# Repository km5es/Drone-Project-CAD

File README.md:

# Drone-Project-3D
This repository contains 3D CAD models, pcb designs, and RF simulation files for a drone-based antenna calibrator entitled Precision Radio Instrument for Antenna Measurements (PRIAM). Its chief application is towards 21-cm cosmology and low-frequency radio instruments. The entire drone-based experiment is represented in the following block diagram:

>[!TIP]
>* A complete [Gitbook](app.gitbook.com) guide can be found here:\
>     https://krishnamakhija.gitbook.io/priam/
>* The repo containing the ROS and SDR code along with the flight path generator can be found [here](https://github.com/km5es/Drone-Project-code.git).

Two drones have been developed, one with a Flamewheel F450 frame and one with a Tarot T960 frame.

## Flamewheel F450

A scaled down drone for experimentation and testing. This was used for testing the custom ROS nodes, RTK performance, and new versions of the flight stack. This was also used to evaluate potential features and upgrades such as RPM-based gyro filtering, and system model verification.

### Drone 
* Flamewheel F450 frame,
* DJI 2312E 960 KV motors,
* DJI 9450 propellers,
* APD 80A F-Series 80F3[X] ESC,
* Pixhawk 2.1 CubeOrange,
* Drotek F9P-based RTK GPS,
* Maxbotix MB1242 SONAR,
* FrSky X8R radio,
* 915 MHz SiK telemetry,
* 4S 4500 mAh Li-Po battery.

### Payload
* ODROID XU4 single-board computer

## PRIAM (Tarot T960)

The actual experiment will be carried out on a larger drone capable of bearing the entire payload. It will be capable of extremely precise magnitude and phase measurements of an antenna-under-test (AUT) using a [custom-developed autonomous calibration routine](https://github.com/km5es/Drone-Project-code). Here are some of its hardware specifications:

### Drone
* Tarot T960 frame,
* APD 80A F-Series 80F3[X] ESC,
* Tarot 5008 High Power Brushless Motor (340kv),
* Tarot 1855 props,
* 12Ah battery -- about 35-40 mins of endurance expected,
* 12 kgs of total weight capacity,
* Retractable landing gear,
* Drotek F9P-based RTK GPS,
* Pixhawk 2.4.8 flight controller,
* 915 MHz SiK telemetry,
* 2.4 GHz X8R radio,
* Maxbotix MB1242 SONAR.

### Payload
* Raspberry Pi 4B payload computer with UPS and separate battery,
* Ettus B205-mini software-defined radio (70 MHz - 6 GHz),
* Custom RF circuitry: RF switch, and dual-pol balun,
* Dual-polarization, half-wavelength, telescopic, crossed-dipoles (70 MHz - 1 GHz),
* High accuracy frequency reference (phase payload)

Complete CAD models and further details are to be found in the [CAD Files](/CAD_Files) folder. That folder also contains drawings and Inventor files for custom parts for both drones. 

In addition, several RF modules have been designed. 

## RF modules
### Switches

Two switches have been designed:
* A simple switch to enable X- and Y- polarization calibration (left) and
* A network of RF switches to enable X-, Y- and circular-polarized calibration (right).

<br><br><br><br><br><br><br><br><br><br><br><br><br><br><br>

### Balun

There is also a dual-pol vertically oriented balun included in this repository. 

<br><br><br><br><br><br><br><br><br><br><br><br><br><br><br><br>
<br><br><br><br>

Microwave Office (MWO), Eagle, and Fusion360 files of these components are included in the [RF Related](/RF_Related) folder. Details of each are in nested `README.md` files. 

>***NOTE:*** Several sub-assemblies and parts in the 3D models have been obtained from [GrabCAD](https://grabcad.com/). None of the work in this repo is towards commercialization or monetary profit. However, credit is due to the creators of those files anyway.

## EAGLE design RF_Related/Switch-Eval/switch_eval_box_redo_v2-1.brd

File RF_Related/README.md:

# RF-related files
This folder contains:
* MWO simulation files of the polarization switch - a network of RF switches, amplifiers, and filters that enables switching from linear X to linear Y polarization and then to circular polarization using the payload computer's GPIO.
* Eagle files for the polarization switch and a simple RF switch which is used for simply switching from linear X to linear Y polarization (for cross-polarization calibration only).
* Eagle, Inventor and Fusion360 files of the dual-pol balun candidates.

## Polarization switch
Below is a block diagram of the full polarization switch. Its purpose is to enable cross-polarization, co-polarization and circular polarization calibrations of the antenna under test. It will also facilitate multipath corrections and improve SNR by 10 dB bringing the total ouput power of the transmitter up to +20 dBm.

There should be three circuit boards: for a low-band (60 - 90 MHz), mid-band (120 - 150 MHz), and a high-band mode (190 - 250 MHz). [This](pol_switch.emp) file has the MWO simulations of the low-band version of the polarization switch. Here are the S-parameters (simulation only) of the low-band switch in circular polarization mode:

The BOM (not comprehensive right now, does not contain Mini Circuits components) is attached [here](ShopCart.csv). 

There is also a simpler version of the switch added [here](Switch-Eval/). This is simply an evaluation board of the [HSWA2-30DR+][switch] switch from Mini Circuits. This will only enable linear-X and linear-Y measurements. The boxes that I have chosen to house the PCBs are linked [here][hammond_box_large] and [here][hammond_box_small]. Fusion360 files soon to follow. This is what the boards look like right now (eval and full pol switch).

<br><br><br><br><br><br><br><br><br><br><br><br><br><br><br>

## Balun
This folder also contains 3D CAD models and Eagle PCB design files of the dual-pol balun. The balun is a vertically oriented dual-pol design using two separate PCBs with a 2:1 turns ratio [transformer][trans]. The box I am considering is linked [here][balun-box]. Here is what it looks like:

[hammond_box_large]: https://www.hammfg.com/part/1590Z062BK?referer=526
[hammond_box_small]: https://www.hammfg.com/part/1590Z061BK
[switch]: https://www.minicircuits.com/WebStore/dashboard.html?model=HSWA2-30DR%2B
[balun-box]: https://www.davantech.com/product/d1001433-electronic-project-box-52w38h80l/
[trans]: https://www.minicircuits.com/WebStore/dashboard.html?model=ADT2-1T%2B

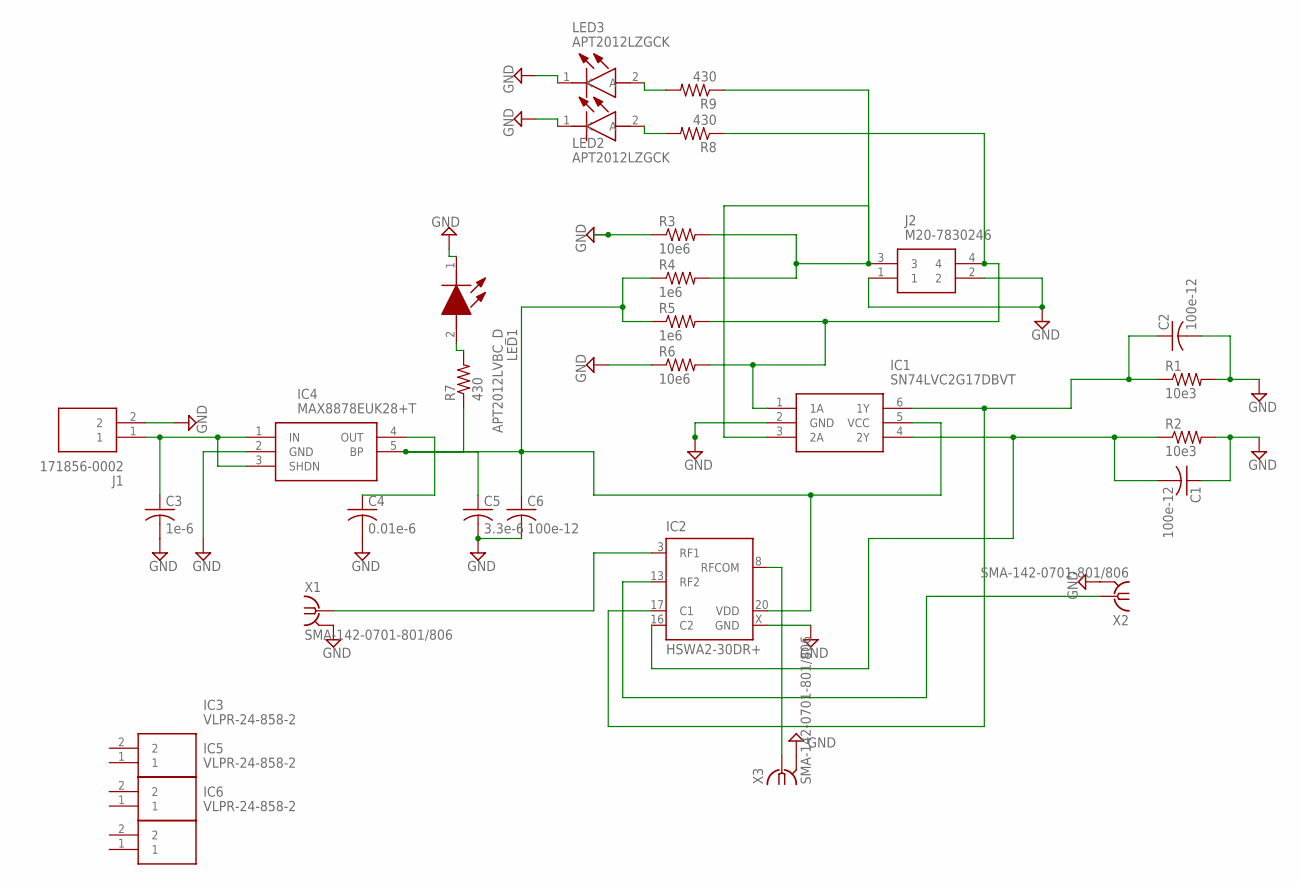
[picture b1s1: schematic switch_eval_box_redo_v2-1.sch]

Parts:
C1, C2, C6: 100e-12; C0603
C3: 1e-6; C0603
C4: 0.01e-6; C0603
C5: 3.3e-6; C0603
IC1: SN74LVC2G17DBVT; SOT95P280X145-6N
IC2: HSWA2-30DR+; DG983-1
IC3, IC5, IC6: VLPR-24-858-2; VLPR248582
IC4: MAX8878EUK28+T; SOT95P280X145-5N
J1: 171856-0002; SHDR2W90P0X254_1X2_493X635X106
J2: M20-7830246; M207830246
LED1: APT2012LVBC_D; LEDC2012X85N
LED2, LED3: APT2012LZGCK; LEDC2012X85N
R1, R2: 10e3; R0603
R3, R6: 10e6; R0603
R4, R5: 1e6; R0603
R7, R8, R9: 430; R0603
X1, X2, X3: SMA-142-0701-801/806; J502-ND-142-0701-801/806

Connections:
GND: C1.1, C2.2, C3.2, C4.2, C5.2, C6.2, IC1.2 (GND), IC2.1 (GND), IC2.2 (GND), IC2.4 (GND), IC2.5 (GND), IC2.6 (GND), IC2.7 (GND), IC2.9 (GND), IC2.10 (GND), IC2.11 (GND), IC2.12 (GND), IC2.14 (GND), IC2.15 (GND), IC2.18 (GND), IC2.19 (GND), IC2.X (GND), IC4.2 (GND), J1.2, J2.1, J2.2, LED1.1 (K), LED2.1 (K), LED3.1 (K), R1.2, R2.2, R3.1, R6.1, X1.G@1 (2), X1.G@2 (2), X1.G@3 (2), X1.G@4 (2), X2.G@1 (2), X2.G@2 (2), X2.G@3 (2), X2.G@4 (2), X3.G@1 (2), X3.G@2 (2), X3.G@3 (2), X3.G@4 (2)
unnamed: IC1.3 (2A), J2.3, R3.2, R4.2, R9.1
unnamed: C3.1, IC4.1 (IN), IC4.3 (SHDN), J1.1
unnamed: C4.1, IC4.4 (OUT)
unnamed: IC1.1 (1A), J2.4, R5.2, R6.2, R8.1
unnamed: LED1.2 (A), R7.2
unnamed: LED3.2 (A), R9.2
unnamed: C5.1, C6.1, IC1.5 (VCC), IC2.20 (VDD), IC4.5 (BP), R4.1, R5.1, R7.1
unnamed: IC2.3 (RF1), X1.1
unnamed: C2.1, IC1.6 (1Y), IC2.17 (C1), R1.1
unnamed: IC2.13 (RF2), X2.1
unnamed: C1.2, IC1.4 (2Y), IC2.16 (C2), R2.1
unnamed: IC2.8 (RFCOM), X3.1
unnamed: LED2.2 (A), R8.2

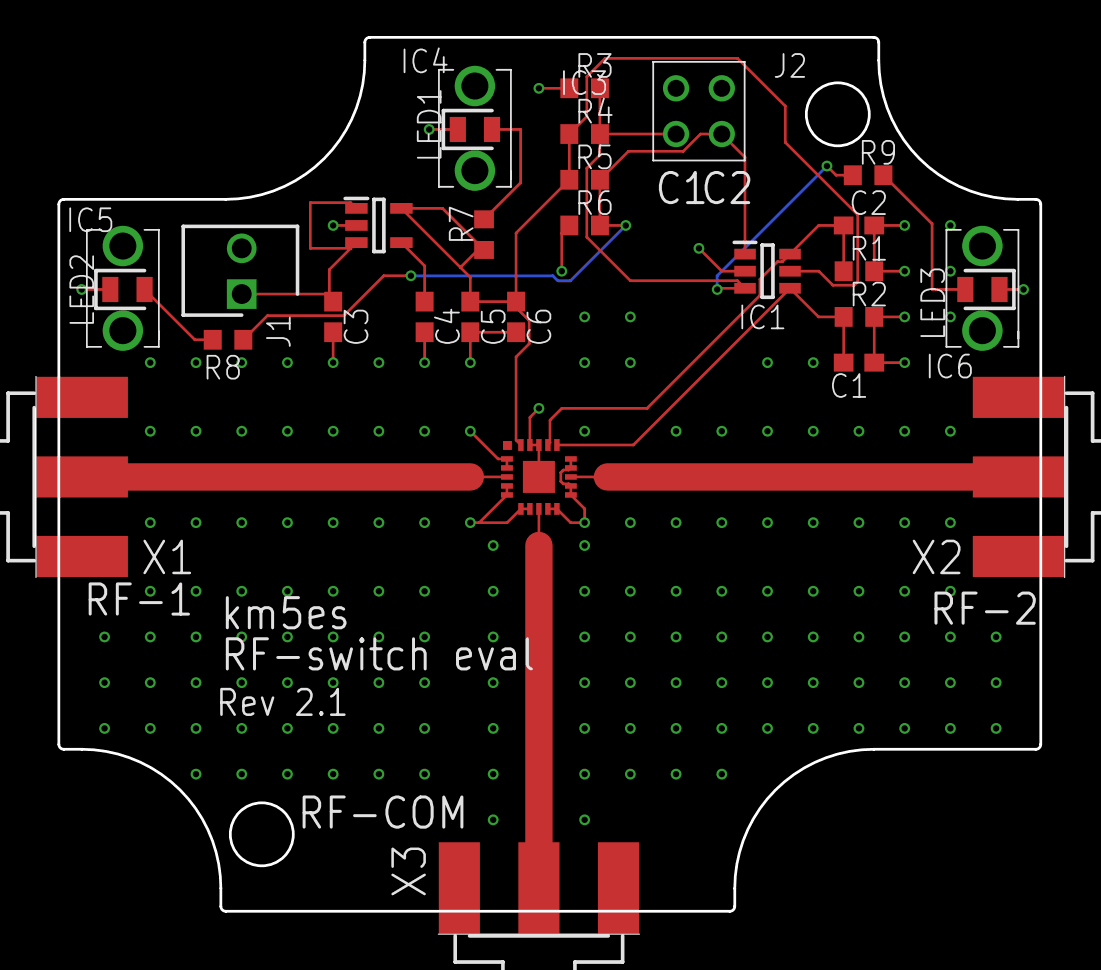
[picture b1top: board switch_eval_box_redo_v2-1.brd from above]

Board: 2 copper layers, 57.2 x 49.8 mm, 29 parts (0 on the bottom side), 14 nets.

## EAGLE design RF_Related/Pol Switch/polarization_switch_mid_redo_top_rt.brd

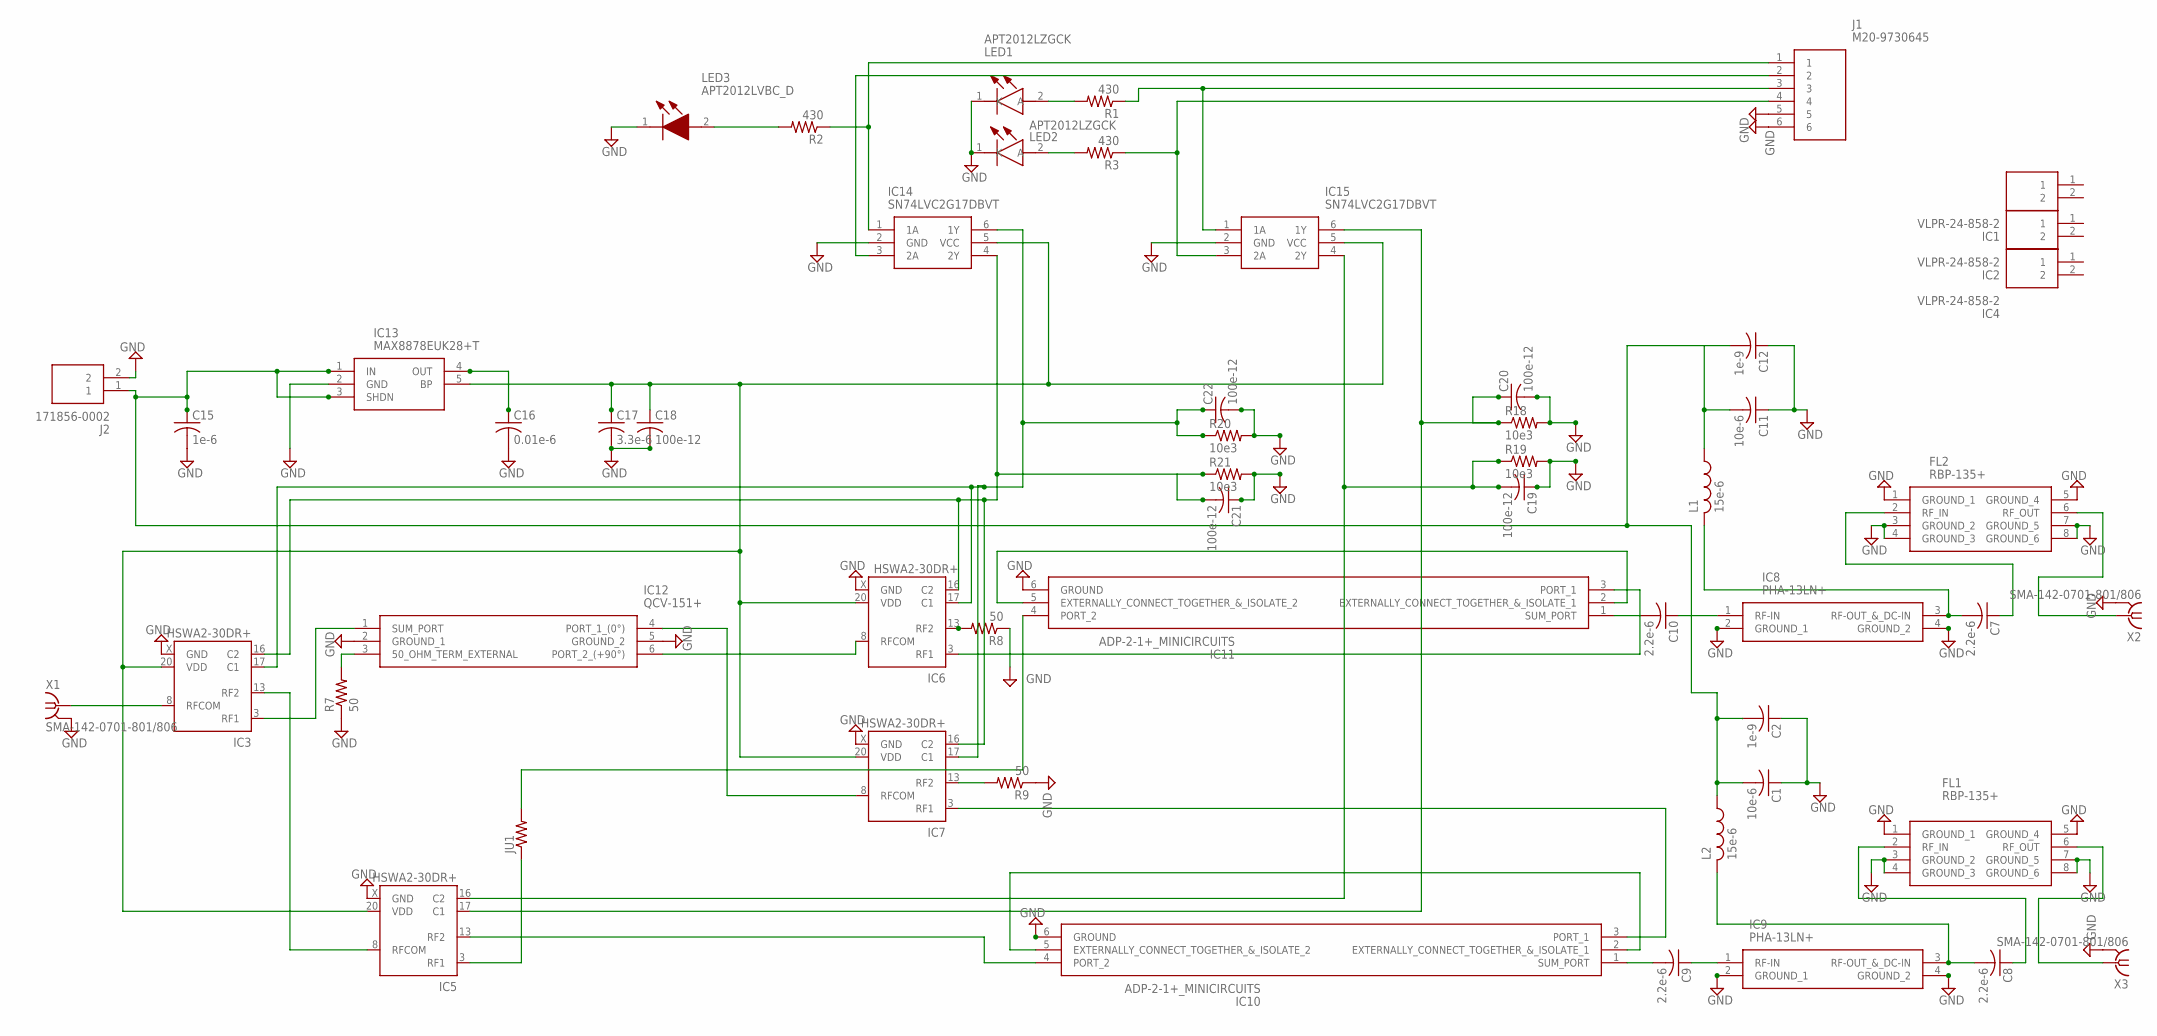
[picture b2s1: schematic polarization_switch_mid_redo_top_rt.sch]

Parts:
C1, C11: 10e-6; C0603
C2, C12: 1e-9; C0603
C7, C8, C9, C10: 2.2e-6; C0603
C15: 1e-6; C0603
C16: 0.01e-6; C0603
C17: 3.3e-6; C0603
C18, C19, C20, C21, C22: 100e-12; C0603
FL1, FL2: RBP-135+; RBP135
IC1, IC2, IC4: VLPR-24-858-2; VLPR248582
IC3, IC5, IC6, IC7: HSWA2-30DR+; DG983-1
IC8, IC9: PHA-13LN+; PHA13LN
IC10, IC11: ADP-2-1+_MINICIRCUITS; SOTFL254P691X411-6N
IC12: QCV-151+; QCV151
IC13: MAX8878EUK28+T; SOT95P280X145-5N
IC14, IC15: SN74LVC2G17DBVT; SOT95P280X145-6N
J1: M20-9730645; HDRV6W66P0X254_1X6_1524X254X96
J2: 171856-0002; SHDR2W90P0X254_1X2_493X635X106
JU1: R-US_R1206; R1206
L1, L2: 15e-6; L3225M
LED1, LED2: APT2012LZGCK; LEDC2012X85N
LED3: APT2012LVBC_D; LEDC2012X85N
R1, R2, R3: 430; R0603
R7, R8, R9: 50; R0603
R18, R19, R20, R21: 10e3; R0603
X1, X2, X3: SMA-142-0701-801/806; J502-ND-142-0701-801/806

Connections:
GND: C1.1, C2.1, C11.1, C12.1, C15.2, C16.2, C17.2, C18.2, C19.1, C20.2, C21.1, C22.2, FL1.1 (GROUND_1), FL1.3 (GROUND_2), FL1.4 (GROUND_3), FL1.5 (GROUND_4), FL1.7 (GROUND_5), FL1.8 (GROUND_6), FL2.1 (GROUND_1), FL2.3 (GROUND_2), FL2.4 (GROUND_3), FL2.5 (GROUND_4), FL2.7 (GROUND_5), FL2.8 (GROUND_6), IC3.1 (GND), IC3.2 (GND), IC3.4 (GND), IC3.5 (GND), IC3.6 (GND), IC3.7 (GND), IC3.9 (GND), IC3.10 (GND), IC3.11 (GND), IC3.12 (GND), IC3.14 (GND), IC3.15 (GND), IC3.18 (GND), IC3.19 (GND), IC3.X (GND), IC5.1 (GND), IC5.2 (GND), IC5.4 (GND), IC5.5 (GND), IC5.6 (GND), IC5.7 (GND), IC5.9 (GND), IC5.10 (GND), IC5.11 (GND), IC5.12 (GND), IC5.14 (GND), IC5.15 (GND), IC5.18 (GND), IC5.19 (GND), IC5.X (GND), IC6.1 (GND), IC6.2 (GND), IC6.4 (GND), IC6.5 (GND), IC6.6 (GND), IC6.7 (GND), IC6.9 (GND), IC6.10 (GND), IC6.11 (GND), IC6.12 (GND), IC6.14 (GND), IC6.15 (GND), IC6.18 (GND), IC6.19 (GND), IC6.X (GND), IC7.1 (GND), IC7.2 (GND), IC7.4 (GND), IC7.5 (GND), IC7.6 (GND), IC7.7 (GND), IC7.9 (GND), IC7.10 (GND), IC7.11 (GND), IC7.12 (GND), IC7.14 (GND), IC7.15 (GND), IC7.18 (GND), IC7.19 (GND), IC7.X (GND), IC8.2 (GROUND_1), IC8.4 (GROUND_2), IC9.2 (GROUND_1), IC9.4 (GROUND_2), IC10.6 (GROUND), IC11.6 (GROUND), IC12.2 (GROUND_1), IC12.5 (GROUND_2), IC13.2 (GND), IC14.2 (GND), IC15.2 (GND), J1.5, J1.6, J2.2, LED1.1 (K), LED2.1 (K), LED3.1 (K), R7.1, R8.1, R9.1, R18.2, R19.2, R20.2, R21.2, X1.G@1 (2), X1.G@2 (2), X1.G@3 (2), X1.G@4 (2), X2.G@1 (2), X2.G@2 (2), X2.G@3 (2), X2.G@4 (2), X3.G@1 (2), X3.G@2 (2), X3.G@3 (2), X3.G@4 (2)
unnamed: LED2.2 (A), R3.2
unnamed: LED1.2 (A), R1.2
unnamed: LED3.2 (A), R2.2
unnamed: IC5.13 (RF2), IC10.4 (PORT_2)
unnamed: IC3.8 (RFCOM), X1.1
unnamed: C10.2, IC11.1 (SUM_PORT)
unnamed: IC7.3 (RF1), IC10.3 (PORT_1)
unnamed: C20.1, IC5.17 (C1), IC15.6 (1Y), R18.1
unnamed: IC7.8 (RFCOM), IC12.4 (PORT_1_(0°))
unnamed: IC11.4 (PORT_2), JU1.2
unnamed: IC6.3 (RF1), IC11.3 (PORT_1)
unnamed: IC5.3 (RF1), JU1.1
unnamed: C10.1, IC8.1 (RF-IN)
unnamed: IC3.3 (RF1), IC12.1 (SUM_PORT)
unnamed: IC3.13 (RF2), IC5.8 (RFCOM)
unnamed: IC6.8 (RFCOM), IC12.6 (PORT_2_(+90°))
unnamed: IC6.13 (RF2), R8.2
unnamed: C7.2, IC8.3 (RF-OUT_&_DC-IN), L1.2
unnamed: C9.2, IC10.1 (SUM_PORT)
unnamed: IC11.2 (EXTERNALLY_CONNECT_TOGETHER_&_ISOLATE_1), IC11.5 (EXTERNALLY_CONNECT_TOGETHER_&_ISOLATE_2)
unnamed: IC10.2 (EXTERNALLY_CONNECT_TOGETHER_&_ISOLATE_1), IC10.5 (EXTERNALLY_CONNECT_TOGETHER_&_ISOLATE_2)
unnamed: C9.1, IC9.1 (RF-IN)
unnamed: C8.2, IC9.3 (RF-OUT_&_DC-IN), L2.2
unnamed: C7.1, FL2.2 (RF_IN)
unnamed: FL2.6 (RF_OUT), X2.1
unnamed: C8.1, FL1.2 (RF_IN)
unnamed: FL1.6 (RF_OUT), X3.1
unnamed: IC12.3 (50_OHM_TERM_EXTERNAL), R7.2
unnamed: IC7.13 (RF2), R9.2
unnamed: C1.2, C2.2, C11.2, C12.2, C15.1, IC13.1 (IN), IC13.3 (SHDN), J2.1, L1.1, L2.1
unnamed: IC14.1 (1A), J1.1, R2.1
unnamed: C19.2, IC5.16 (C2), IC15.4 (2Y), R19.1
unnamed: C17.1, C18.1, IC3.20 (VDD), IC5.20 (VDD), IC6.20 (VDD), IC7.20 (VDD), IC13.5 (BP), IC14.5 (VCC), IC15.5 (VCC)
unnamed: C16.1, IC13.4 (OUT)
unnamed: C22.1, IC3.17 (C1), IC6.17 (C1), IC7.17 (C1), IC14.6 (1Y), R20.1
unnamed: IC14.3 (2A), J1.2
unnamed: IC15.1 (1A), J1.3, R1.1
unnamed: IC15.3 (2A), J1.4, R3.1
unnamed: C21.2, IC3.16 (C2), IC6.16 (C2), IC7.16 (C2), IC14.4 (2Y), R21.1

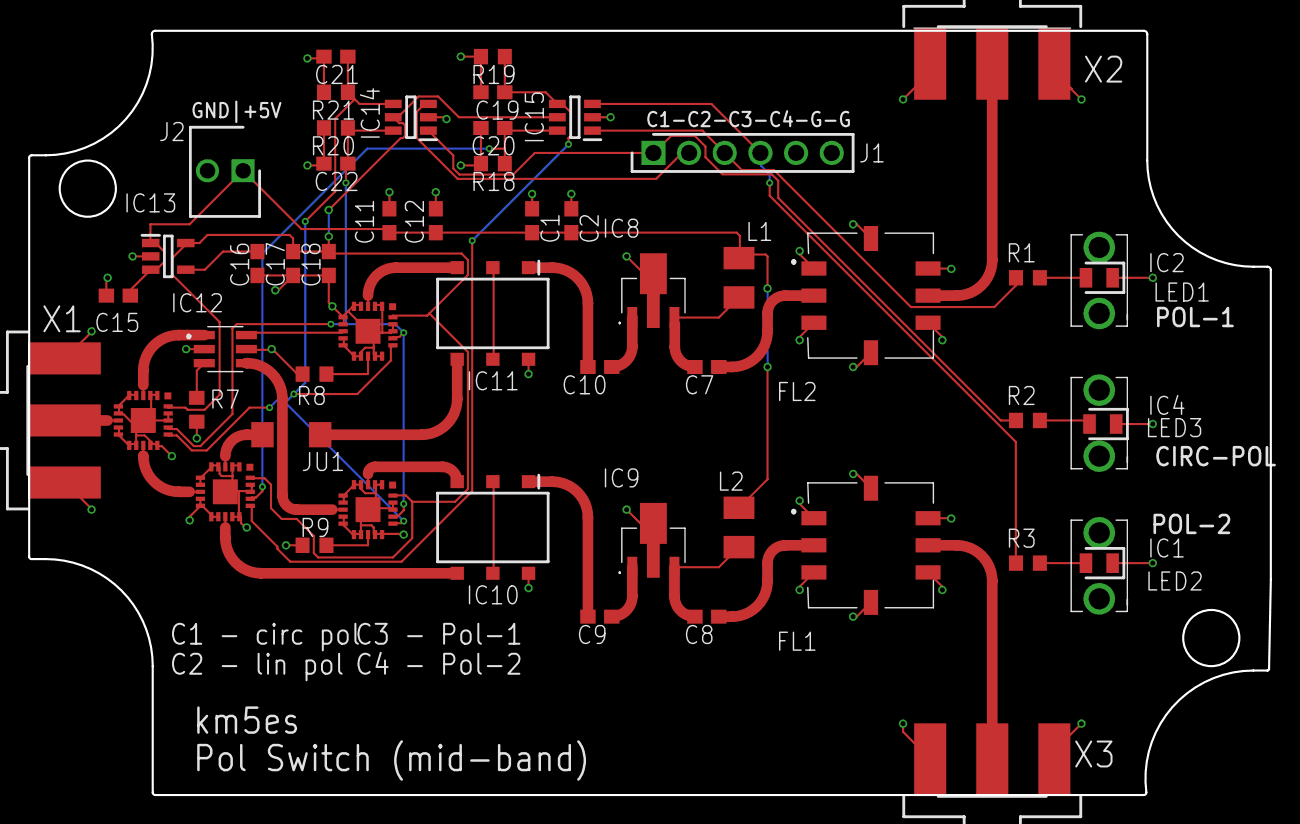
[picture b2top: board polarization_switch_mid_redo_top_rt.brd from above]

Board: 2 copper layers, 88.4 x 54.4 mm, 54 parts (0 on the bottom side), 40 nets.

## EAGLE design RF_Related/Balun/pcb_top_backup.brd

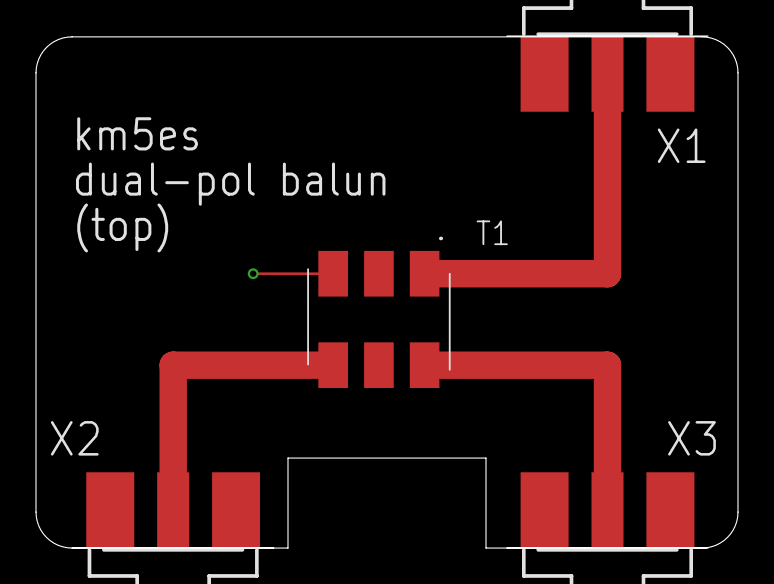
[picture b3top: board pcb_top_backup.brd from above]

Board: 2 copper layers, 39.0 x 28.4 mm, 4 parts (0 on the bottom side), 4 nets.

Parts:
T1: ADT1-1WT+; ADT11WT
X1, X2, X3: SMA-142-0711-821/826; J502-ND-142-0711-821/826

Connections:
GND: T1.3, X1.G@1, X1.G@2, X1.G@3, X1.G@4, X2.G@1, X2.G@2, X2.G@3, X2.G@4, X3.G@1, X3.G@2, X3.G@3, X3.G@4
unnamed: T1.1, X1.1
unnamed: T1.6, X3.1
unnamed: T1.4, X2.1

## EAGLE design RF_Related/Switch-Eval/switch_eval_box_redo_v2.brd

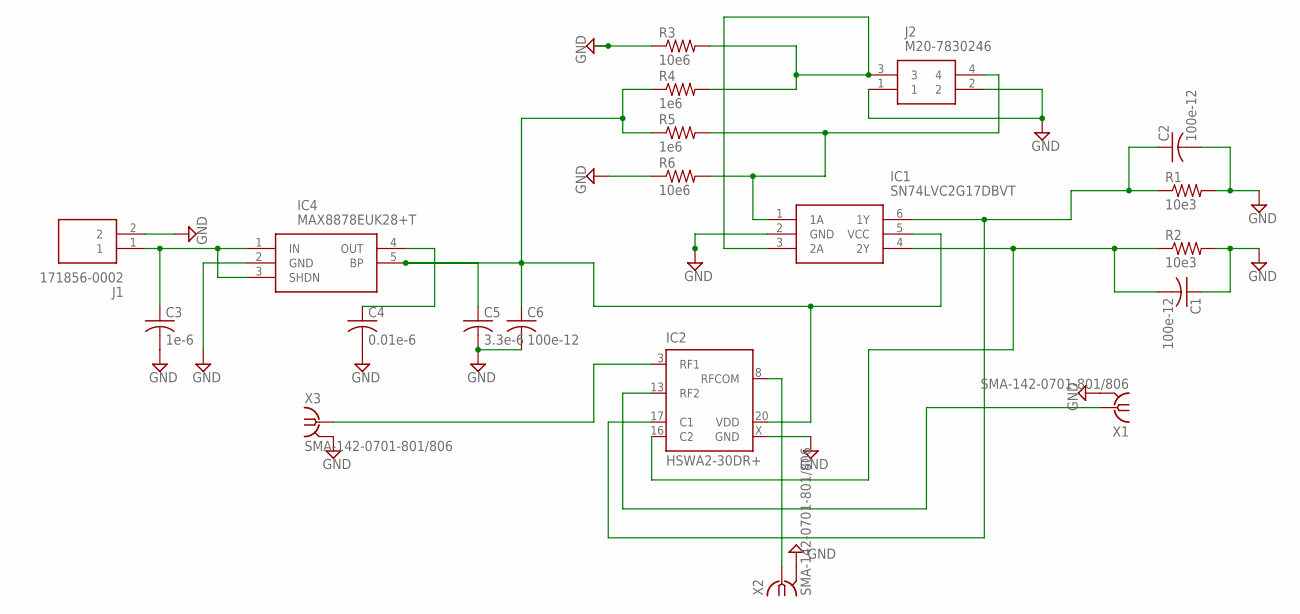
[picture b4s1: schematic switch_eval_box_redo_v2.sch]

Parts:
C1, C2, C6: 100e-12; C0603
C3: 1e-6; C0603
C4: 0.01e-6; C0603
C5: 3.3e-6; C0603
IC1: SN74LVC2G17DBVT; SOT95P280X145-6N
IC2: HSWA2-30DR+; DG983-1
IC4: MAX8878EUK28+T; SOT95P280X145-5N
J1: 171856-0002; SHDR2W90P0X254_1X2_493X635X106
J2: M20-7830246; M207830246
R1, R2: 10e3; R0603
R3, R6: 10e6; R0603
R4, R5: 1e6; R0603
X1, X2, X3: SMA-142-0701-801/806; J502-ND-142-0701-801/806

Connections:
GND: C1.1, C2.2, C3.2, C4.2, C5.2, C6.2, IC1.2 (GND), IC2.1 (GND), IC2.2 (GND), IC2.4 (GND), IC2.5 (GND), IC2.6 (GND), IC2.7 (GND), IC2.9 (GND), IC2.10 (GND), IC2.11 (GND), IC2.12 (GND), IC2.14 (GND), IC2.15 (GND), IC2.18 (GND), IC2.19 (GND), IC2.X (GND), IC4.2 (GND), J1.2, J2.1, J2.2, R1.2, R2.2, R3.1, R6.1, X1.G@1 (2), X1.G@2 (2), X1.G@3 (2), X1.G@4 (2), X2.G@1 (2), X2.G@2 (2), X2.G@3 (2), X2.G@4 (2), X3.G@1 (2), X3.G@2 (2), X3.G@3 (2), X3.G@4 (2)
unnamed: IC1.3 (2A), J2.3, R3.2, R4.2
unnamed: C3.1, IC4.1 (IN), IC4.3 (SHDN), J1.1
unnamed: C4.1, IC4.4 (OUT)
unnamed: IC1.1 (1A), J2.4, R5.2, R6.2
unnamed: C5.1, C6.1, IC1.5 (VCC), IC2.20 (VDD), IC4.5 (BP), R4.1, R5.1
unnamed: IC2.3 (RF1), X3.1
unnamed: C2.1, IC1.6 (1Y), IC2.17 (C1), R1.1
unnamed: IC2.13 (RF2), X1.1
unnamed: C1.2, IC1.4 (2Y), IC2.16 (C2), R2.1
unnamed: IC2.8 (RFCOM), X2.1

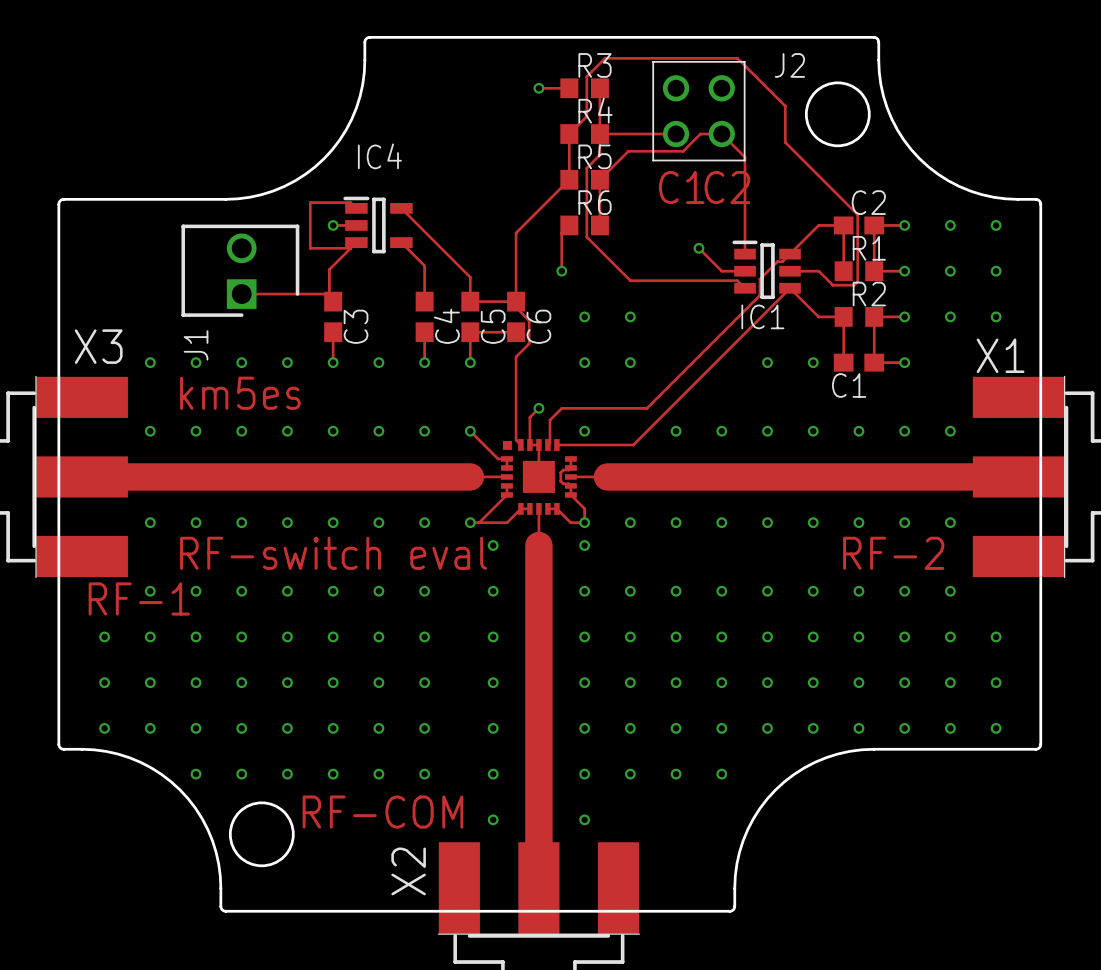
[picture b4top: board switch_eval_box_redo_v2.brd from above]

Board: 2 copper layers, 57.2 x 49.8 mm, 20 parts (0 on the bottom side), 11 nets.

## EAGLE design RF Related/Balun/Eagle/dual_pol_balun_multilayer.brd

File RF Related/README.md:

# RF-related files
This folder contains:
* MWO simulation files of the polarization switch - a network of RF switches, amplifiers, and filters that enables switching from linear X to linear Y polarization and then to circular polarization using the payload computer's GPIO.
* Eagle files for the polarization switch and a simple RF switch which is used for simply switching from linear X to linear Y polarization (for cross-polarization calibration only).
* Eagle, Inventor and Fusion360 files of the dual-pol balun candidates.

## Polarization switch
Below is a block diagram of the full polarization switch. Its purpose is to enable cross-polarization, co-polarization and circular polarization calibrations of the antenna under test. It will also facilitate multipath corrections and improve SNR by 10 dB bringing the total ouput power of the transmitter up to +20 dBm.

There should be three circuit boards: for a low-band (60 - 90 MHz), mid-band (120 - 150 MHz), and a high-band mode (190 - 250 MHz). [This](pol_switch.emp) file has the MWO simulations of the low-band version of the polarization switch. Here are the S-parameters (simulation only) of the low-band switch in circular polarization mode:

The BOM (not comprehensive right now, does not contain Mini Circuits components) is attached [here](ShopCart.csv). 

There is also a simpler version of the switch added [here](Switch-Eval/). This is simply an evaluation board of the [HSWA2-30DR+][switch] switch from Mini Circuits. This will only enable linear-X and linear-Y measurements. The boxes that I have chosen to house the PCBs are linked [here][hammond_box_large] and [here][hammond_box_small]. Fusion360 files soon to follow. This is what the boards look like right now (eval and full pol switch).

\
\
\
\
\
\
\
\
\
\
\
\
\
\
\

## Balun
This folder also contains 3D CAD models and Eagle PCB design files of the dual-pol balun. For now, the current balun candidate is a vertically oriented dual-pol design using two separate PCBs with a 1:1 turns ratio [transformer][trans]. The box I am considering is linked [here][balun-box]. Here is what the current design looks like:

[hammond_box_large]: https://www.hammfg.com/part/1590Z062BK?referer=526
[hammond_box_small]: https://www.hammfg.com/part/1590Z061BK
[switch]: https://www.minicircuits.com/WebStore/dashboard.html?model=HSWA2-30DR%2B
[balun-box]: https://www.davantech.com/product/d1001433-electronic-project-box-52w38h80l/
[trans]: https://www.minicircuits.com/WebStore/dashboard.html?model=ADT1-1%2B

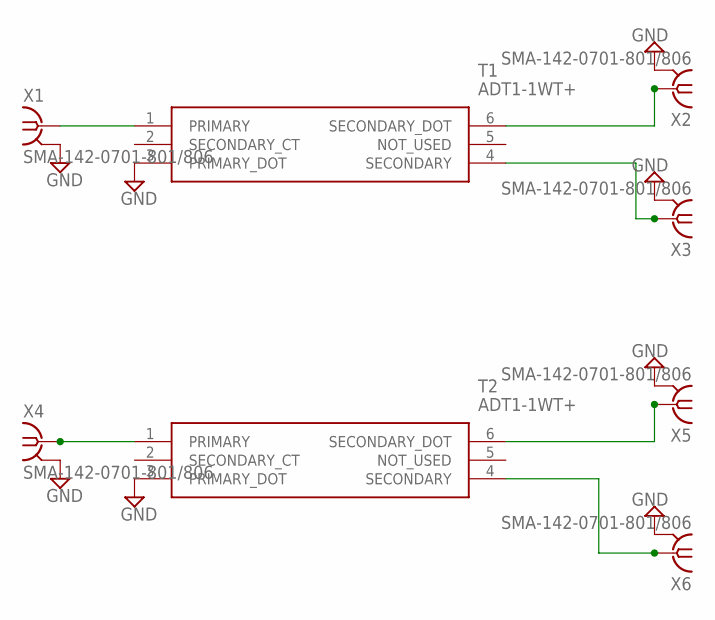
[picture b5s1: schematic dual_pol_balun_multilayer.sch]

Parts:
T1, T2: ADT1-1WT+; ADT11WT
X1, X2, X3, X4, X5, X6: SMA-142-0701-801/806; J502-ND-142-0701-801/806

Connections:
GND: T1.3 (PRIMARY_DOT), T2.3 (PRIMARY_DOT), X1.G@1 (2), X1.G@2 (2), X1.G@3 (2), X1.G@4 (2), X2.G@1 (2), X2.G@2 (2), X2.G@3 (2), X2.G@4 (2), X3.G@1 (2), X3.G@2 (2), X3.G@3 (2), X3.G@4 (2), X4.G@1 (2), X4.G@2 (2), X4.G@3 (2), X4.G@4 (2), X5.G@1 (2), X5.G@2 (2), X5.G@3 (2), X5.G@4 (2), X6.G@1 (2), X6.G@2 (2), X6.G@3 (2), X6.G@4 (2)
unnamed: T1.1 (PRIMARY), X1.1
unnamed: T1.6 (SECONDARY_DOT), X2.1
unnamed: T1.4 (SECONDARY), X3.1
unnamed: T2.1 (PRIMARY), X4.1
unnamed: T2.6 (SECONDARY_DOT), X5.1
unnamed: T2.4 (SECONDARY), X6.1

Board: 4 copper layers, 8 parts (4 on the bottom side), 7 nets, no tracks yet.

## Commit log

2020-08-10 first commit. made dummy folders for CAD and RF stuff.
2020-08-13 added retractable landing skids, F450 GPS mount, navio vibration dampener, and template for payload bay.
2020-08-13 added the correct F450 gps mount files.
2020-08-13 documentation and MWO files.
2020-08-14 added eagle files. however, board and actual eagle project are still separate.
2020-08-14 added fusion360 files as well.
2020-08-14 added CAD files made by Varundev for the battery mount and PDB.
2020-08-20 created GPS mount and dwg file for square payload bay. the GPS mount does not have holes for the GPSDO antenna and payload bay does not have holes for payload right now.
2020-08-31 Big update. made changes to existing brackets. made cutouts for straps and cables. also added the entire drone model in Inventor.
2020-09-01 the GPS mount and battery mount now have imperial units holes for new standoffs. also modified the entire model to have accurate arms, motors, and ESCs.
2020-09-04 pdb mount now has correctly spaced holes for mounting on central hub.
2020-09-26 made first draft of a balun. also made switch-eval but that is not included in this commit.
2020-09-27 made a dual pol balun in Fusion360. Looks really cool. However, the notch is off a little. Backing up before making changes.
2020-09-28 some progress towards pol switch. added switch eval. no balun yet.
2020-09-28 finished both switches. only need to fix the connector issue and the balun.
2020-09-28 redoing the routing again for pol switch. making backup now.
2020-09-30 about to start making a multilayer balun and modifications to the SMA connector pads.
2020-10-01 also updated entire drone 3D model to contain primary balun candidate.
2020-10-02 added eagle, and fusion360 files for the vertical dual pol balun. need to make fine measurements to confirm it is okay though.
2020-10-02 updated README in RF Related.
2020-10-02 updated main README.
2020-10-28 added balun. retractable landing skids, better models of the entire drone after rescaling and so much more!
2020-11-13 changed a whole lot. all the inventor files for the T960 (PRIAM) are now on Google Drive again. Made a Fusion360 model of the F450 and the T960. This repo only contains those files along with custom 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
2020-11-13 made small changes to README files.
2020-11-13 more changes to README files.
2020-11-13 changes to main README.
2020-11-13 more refinements to README. corrected some typos and added disclaimer about grabcad.
2020-11-13 cleaned out the balun folder and added RF components to main README.
2020-11-13 formatting issues.
2020-11-16 readme has more headings and is more structured.
2020-12-07 added balun interactive image from cadasio.
2020-12-07 added balun interactive image from cadasio. making changes.
2020-12-07 rolling back on the 3D embed. didn't work.
2020-12-28 balun is ready. do final checks on other boards before sending them in. 3D model of drone now has GPSDO antenna and more in the payload.
2020-12-28 README files now show new models on drone. balun not yet updated.
2021-01-30 doing a second revision of balun boards. going to do another rev of the payload bays soon.
2021-02-26 tested switches. balun seems okay at first blush.
2021-06-22 saving before making changes to balun
2021-08-11 updated PRIAM gif and other small changes
2021-09-23 backing up before making changes to the pol switch board
2021-10-04 made a new pol switch board with jumper pads. do I need that resistor row? backing up now
2021-10-06 made a new version of the pol switch. already sent to OSH park for fab. note that there is a template for routing as well as a completed circuit
2022-01-03 made a new revision of the simple RF switch and sent it to fab.
2023-05-23 starting to add finishing touches here. will take several commits
2023-05-23 loads of housekeeping. added most of the final 3d parts and moved them inside folders for organization
2023-05-23 resizing f450 gif
2023-05-23 added updated fusion model of mag drone. deleted OldVersions from previous Inventor models
2023-05-23 added updated photos of drone deployment, and priam-p
2023-05-23 housekeeping in the RF_Related section
2023-05-28 updated block diagram
